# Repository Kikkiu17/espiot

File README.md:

# espiot
A small board built to measure current and voltage of an appliance.<br />
This board was used as a testbed for STM32 ADC oversampler, UART and DMA.<br />
To measure current and voltage values, a 12-bit ADC was used, with an oversampling ratio of 256x and an 8-bit shift to obtain efficient data averaging - this provides stable readings, along with a sampling time of 3.5 cycles for current and 79.5 cycles for voltage. DMA was also used to transfer all the ADC readings into memory without performance losses.

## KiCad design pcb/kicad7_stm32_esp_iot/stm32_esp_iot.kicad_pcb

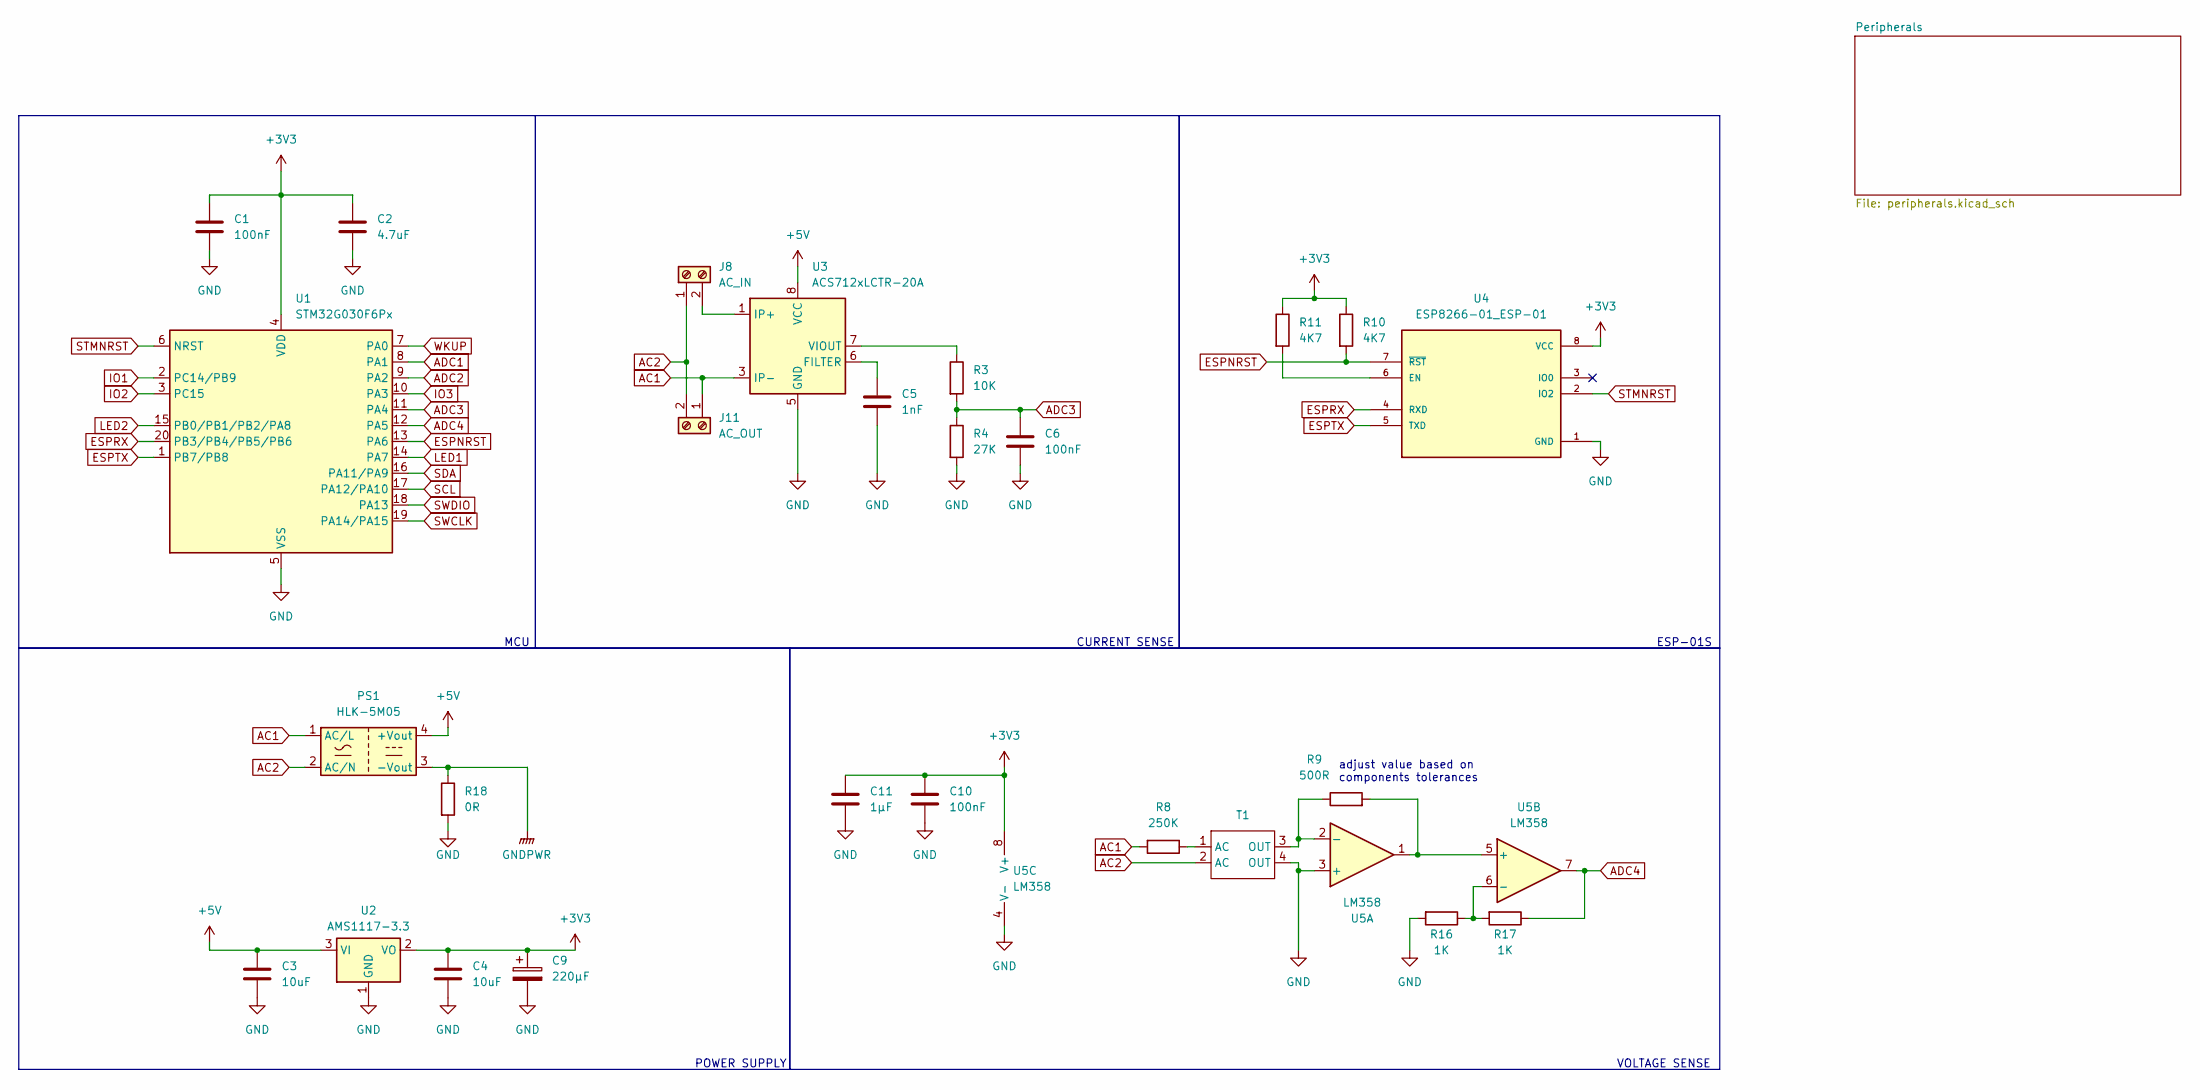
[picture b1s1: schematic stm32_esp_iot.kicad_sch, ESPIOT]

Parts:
C1, C6, C10: 100nF; C_0603_1608Metric
C2: 4.7uF; C_0603_1608Metric
C3, C4: 10uF; C_0603_1608Metric
C5: 1nF; C_0603_1608Metric
C9: 220µF; CP_Radial_D6.3mm_P2.50mm
C11: 1µF; C_0603_1608Metric
J8: AC_IN; mors_2p
J11: AC_OUT; mors_2p
PS1: HLK-5M05; Converter_ACDC_HiLink_HLK-5Mxx
R3: 10K; R_0603_1608Metric
R4: 27K; R_0603_1608Metric
R8: 250K; R_1206_3216Metric
R9: 500R; R_0603_1608Metric
R10, R11: 4K7; R_0603_1608Metric
R16, R17: 1K; R_0603_1608Metric
R18: 0R; R_1206_3216Metric
T1: ZMPT107
U1: STM32G030F6Px; TSSOP-20_4.4x6.5mm_P0.65mm
U2: AMS1117-3.3; SOT-223-3_TabPin2
U3: ACS712xLCTR-20A; SOIC-8_3.9x4.9mm_P1.27mm
U4: ESP8266-01_ESP-01; esp-01s; PARTREV V1.2
U5: LM358; DIP-8_W7.62mm

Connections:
+3V3: C1.1, C2.1, C4.1, C9.1, C10.1, C11.1, R10.1, R11.1, U1.4 (VDD), U2.2 (VO), U4.8 (VCC), U5.8 (V+); also elsewhere on the board
+5V: C3.1, PS1.4 (+Vout), U2.3 (VI), U3.8 (VCC); also elsewhere on the board
AC1: J11.1, PS1.1 (AC/L), R8.2, U3.3 (IP-), U3.4 (IP-)
AC2: J8.1, J11.2, PS1.2 (AC/N), T1.2 (AC)
ADC1: U1.8 (PA1); also elsewhere on the board
ADC2: U1.9 (PA2); also elsewhere on the board
ADC3: C6.1, R3.2, R4.1, U1.11 (PA4)
ADC4: R17.1, U1.12 (PA5), U5.7
ESPNRST: R10.2, U1.13 (PA6), U4.7 (~RST)
ESPRX: U1.20 (PB3/PB4/PB5/PB6), U4.4 (RXD)
ESPTX: U1.1 (PB7/PB8), U4.5 (TXD)
GND: C1.2, C2.2, C3.2, C4.2, C5.2, C6.2, C9.2, C10.2, C11.2, R4.2, R16.2, R18.2, T1.4 (OUT), U1.5 (VSS), U2.1 (GND), U3.5 (GND), U4.1 (GND), U5.3 (+), U5.4 (V-); also elsewhere on the board
GNDPWR: PS1.3 (-Vout), R18.1; also elsewhere on the board
IO1: U1.2 (PC14/PB9); also elsewhere on the board
IO2: U1.3 (PC15); also elsewhere on the board
IO3: U1.10 (PA3); also elsewhere on the board
LED1: U1.14 (PA7); also elsewhere on the board
LED2: U1.15 (PB0/PB1/PB2/PA8); also elsewhere on the board
unnamed: J8.2, U3.1 (IP+), U3.2 (IP+)
unnamed: R8.1, T1.1 (AC)
unnamed: C5.1, U3.6 (FILTER)
unnamed: R3.1, U3.7 (VIOUT)
unnamed: R11.2, U4.6 (EN)
unnamed: R9.1, T1.3 (OUT), U5.2 (-)
unnamed: R9.2, U5.1, U5.5 (+)
unnamed: R16.1, R17.2, U5.6 (-)
SCL: U1.17 (PA12/PA10); also elsewhere on the board
SDA: U1.16 (PA11/PA9); also elsewhere on the board
STMNRST: U1.6 (NRST), U4.2 (IO2)
SWCLK: U1.19 (PA14/PA15); also elsewhere on the board
SWDIO: U1.18 (PA13); also elsewhere on the board
WKUP: U1.7 (PA0); also elsewhere on the board

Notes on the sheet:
adjust value based on components tolerances
MCU
VOLTAGE SENSE
CURRENT SENSE
ESP-01S
POWER SUPPLY

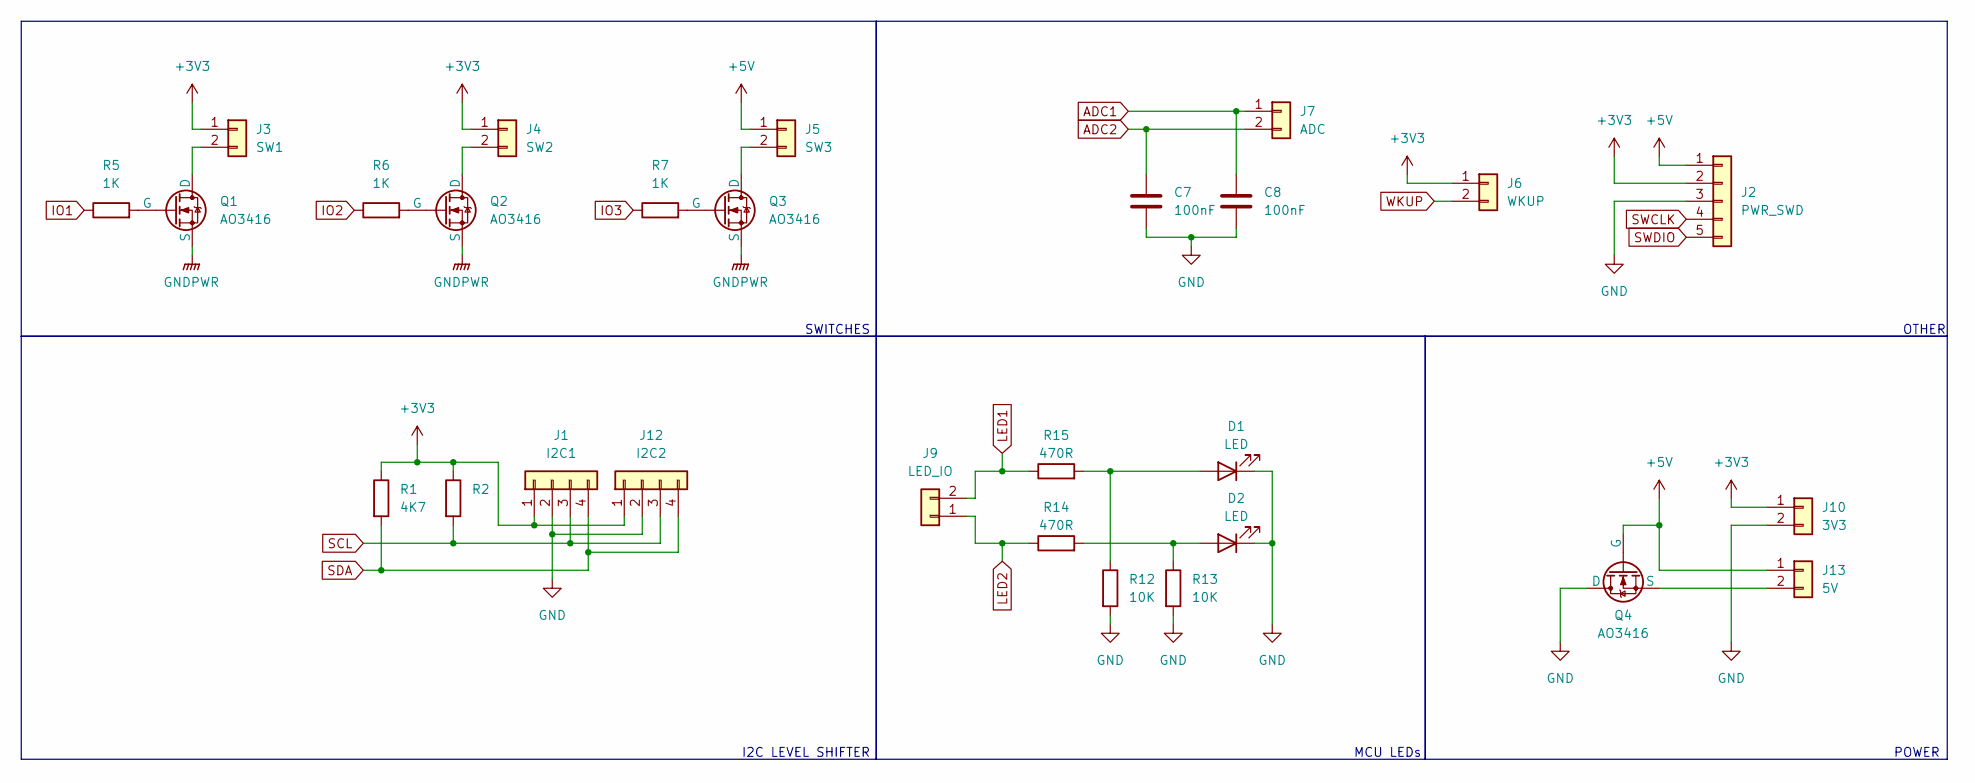
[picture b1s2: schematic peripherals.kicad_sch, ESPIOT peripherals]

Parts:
C7, C8: 100nF; C_0603_1608Metric
D1: LED; LED_0805_2012Metric
D2: LED; LED_0603_1608Metric
J1: I2C1; JST_EH_B4B-EH-A_1x04_P2.50mm_Vertical
J2: PWR_SWD; JST_EH_B5B-EH-A_1x05_P2.50mm_Vertical
J3: SW1; JST_EH_B2B-EH-A_1x02_P2.50mm_Vertical
J4: SW2; JST_EH_B2B-EH-A_1x02_P2.50mm_Vertical
J5: SW3; JST_EH_B2B-EH-A_1x02_P2.50mm_Vertical
J6: WKUP; JST_EH_B2B-EH-A_1x02_P2.50mm_Vertical
J7: ADC; JST_EH_B2B-EH-A_1x02_P2.50mm_Vertical
J9: LED_IO; JST_EH_B2B-EH-A_1x02_P2.50mm_Vertical
J10: 3V3; JST_EH_B2B-EH-A_1x02_P2.50mm_Vertical
J12: I2C2; JST_EH_B4B-EH-A_1x04_P2.50mm_Vertical
J13: 5V; JST_EH_B2B-EH-A_1x02_P2.50mm_Vertical
Q1, Q2, Q3, Q4: AO3416; SOT-23
R1, R2: 4K7; R_0603_1608Metric
R5, R6, R7: 1K; R_0603_1608Metric
R12, R13: 10K; R_0603_1608Metric
R14, R15: 470R; R_0603_1608Metric

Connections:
+3V3: J1.1, J2.2, J3.1, J4.1, J6.1, J10.1, J12.1, R1.1, R2.1; also elsewhere on the board
+5V: J2.1, J5.1, J13.1, Q4.2 (G); also elsewhere on the board
ADC1: C8.1, J7.1; also elsewhere on the board
ADC2: C7.1, J7.2; also elsewhere on the board
GND: C7.2, C8.2, D1.1 (K), D2.1 (K), J1.2, J2.3, J10.2, J12.2, Q4.1 (D), R12.2, R13.2; also elsewhere on the board
GNDPWR: Q1.3 (S), Q2.3 (S), Q3.3 (S); also elsewhere on the board
IO1: R5.1; also elsewhere on the board
IO2: R6.1; also elsewhere on the board
IO3: R7.1; also elsewhere on the board
LED1: J9.2, R15.1; also elsewhere on the board
LED2: J9.1, R14.1; also elsewhere on the board
unnamed: D1.2 (A), R12.1, R15.2
unnamed: D2.2 (A), R13.1, R14.2
unnamed: J3.2, Q1.1 (D)
unnamed: J4.2, Q2.1 (D)
unnamed: J5.2, Q3.1 (D)
unnamed: J13.2, Q4.3 (S)
unnamed: Q1.2 (G), R5.2
unnamed: Q2.2 (G), R6.2
unnamed: Q3.2 (G), R7.2
SCL: J1.3, J12.3, R2.2; also elsewhere on the board
SDA: J1.4, J12.4, R1.2; also elsewhere on the board
SWCLK: J2.4; also elsewhere on the board
SWDIO: J2.5; also elsewhere on the board
WKUP: J6.2; also elsewhere on the board

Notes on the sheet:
POWER
SWITCHES
MCU LEDs
I2C LEVEL SHIFTER
OTHER

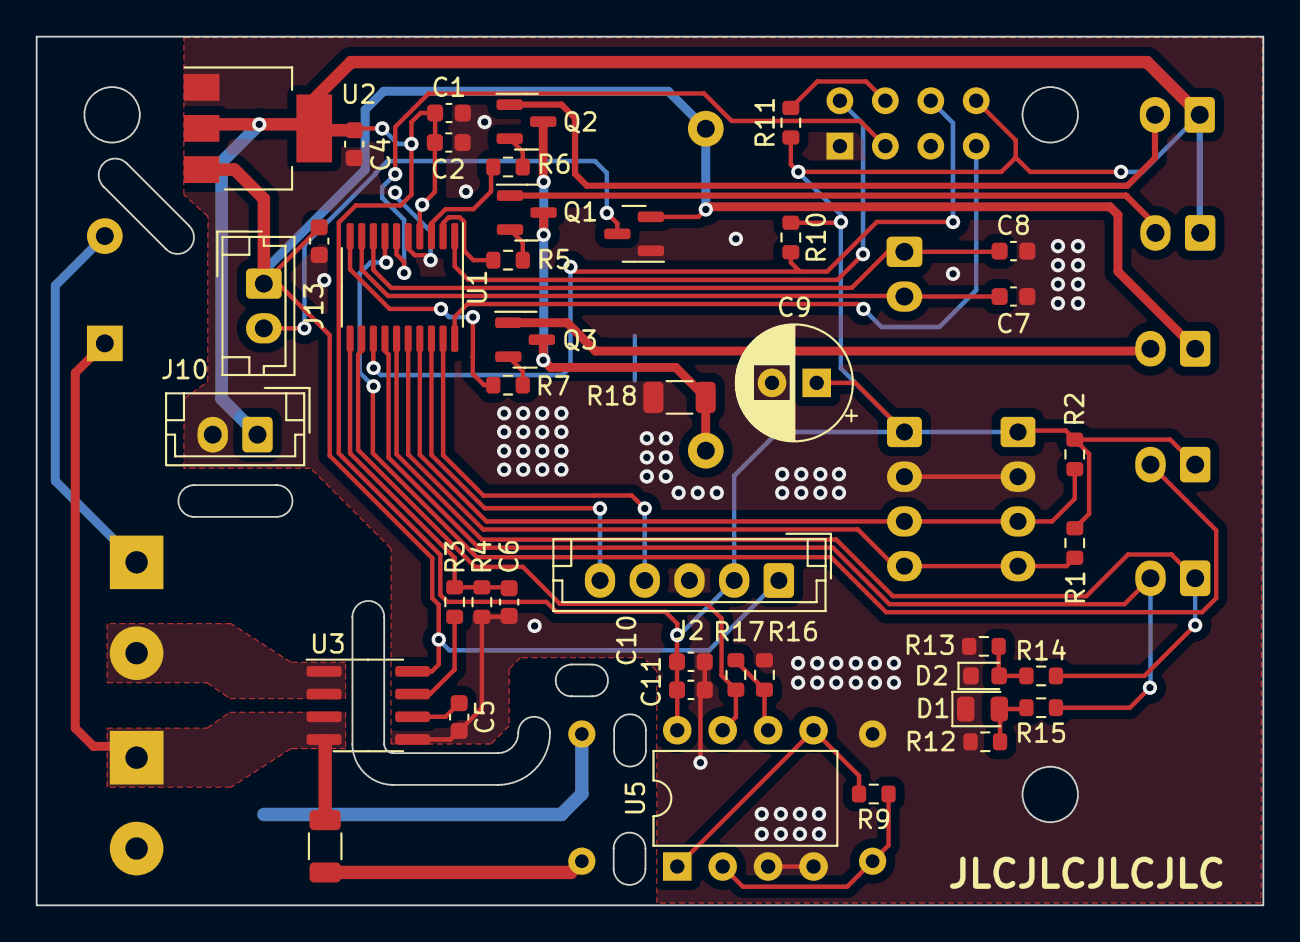
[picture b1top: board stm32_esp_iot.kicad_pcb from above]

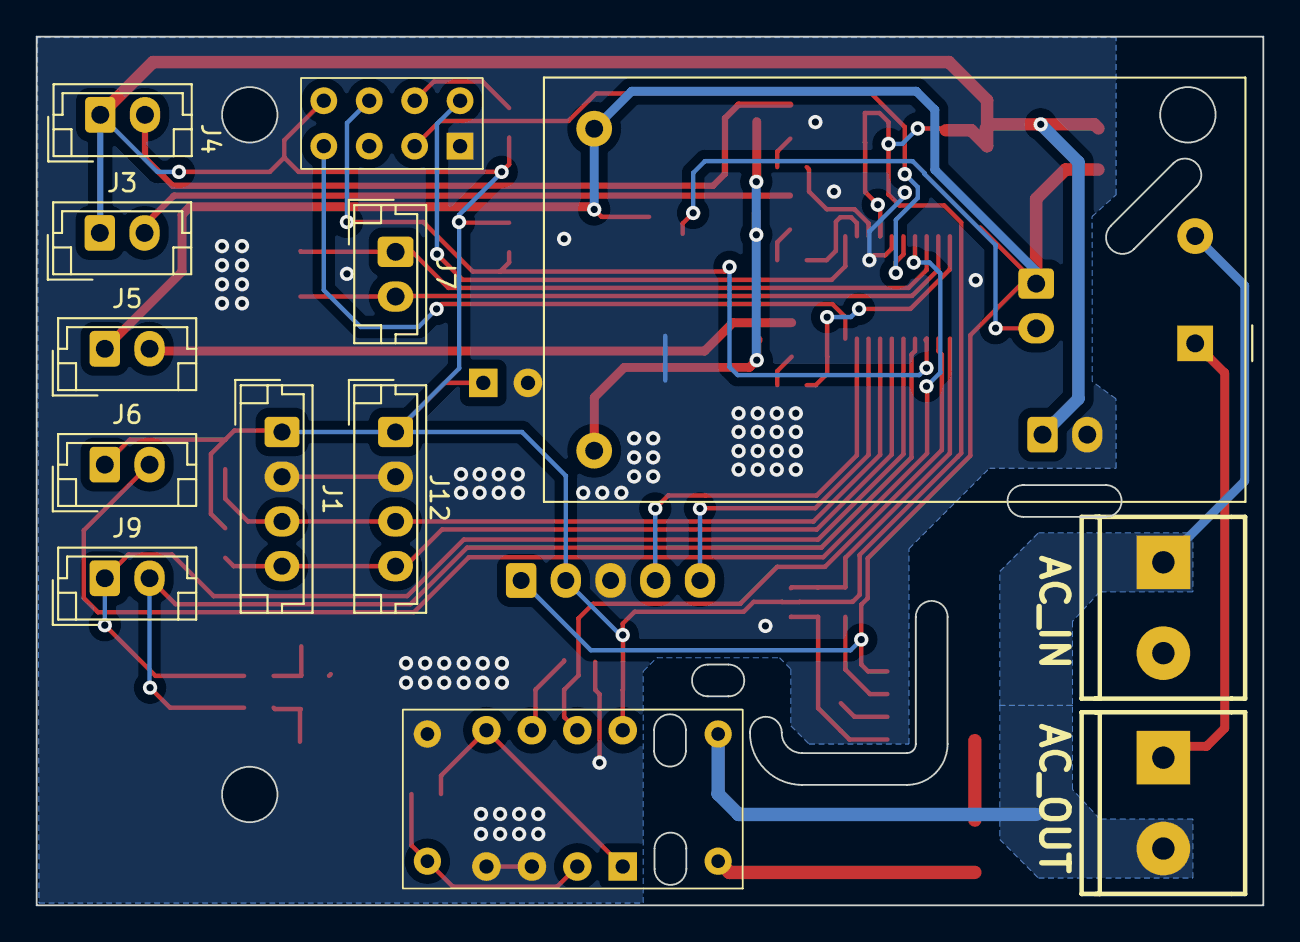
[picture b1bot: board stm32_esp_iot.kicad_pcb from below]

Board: 2 copper layers, 68.6 x 48.6 mm, 55 parts (13 on the bottom side), 41 nets.

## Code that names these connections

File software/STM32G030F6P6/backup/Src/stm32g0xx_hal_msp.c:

/* USER CODE BEGIN Header */
/**
  ******************************************************************************
  * @file         stm32g0xx_hal_msp.c
  * @brief        This file provides code for the MSP Initialization
  *               and de-Initialization codes.
  ******************************************************************************
  * @attention
  *
  * Copyright (c) 2024 STMicroelectronics.
  * All rights reserved.
  *
  * This software is licensed under terms that can be found in the LICENSE file
  * in the root directory of this software component.
  * If no LICENSE file comes with this software, it is provided AS-IS.
  *
  ******************************************************************************
  */
/* USER CODE END Header */

/* Includes ------------------------------------------------------------------*/
#include "main.h"

/* USER CODE BEGIN Includes */

/* USER CODE END Includes */
extern DMA_HandleTypeDef hdma_adc1;

extern DMA_HandleTypeDef hdma_usart1_rx;

/* Private typedef -----------------------------------------------------------*/
/* USER CODE BEGIN TD */

/* USER CODE END TD */

/* Private define ------------------------------------------------------------*/
/* USER CODE BEGIN Define */

/* USER CODE END Define */

/* Private macro -------------------------------------------------------------*/
/* USER CODE BEGIN Macro */

/* USER CODE END Macro */

/* Private variables ---------------------------------------------------------*/
/* USER CODE BEGIN PV */

/* USER CODE END PV */

/* Private function prototypes -----------------------------------------------*/
/* USER CODE BEGIN PFP */

/* USER CODE END PFP */

/* External functions --------------------------------------------------------*/
/* USER CODE BEGIN ExternalFunctions */

/* USER CODE END ExternalFunctions */

/* USER CODE BEGIN 0 */

/* USER CODE END 0 */
/**
  * Initializes the Global MSP.
  */
void HAL_MspInit(void)
{
  /* USER CODE BEGIN MspInit 0 */

  /* USER CODE END MspInit 0 */

  __HAL_RCC_SYSCFG_CLK_ENABLE();
  __HAL_RCC_PWR_CLK_ENABLE();

  /* System interrupt init*/

  /* USER CODE BEGIN MspInit 1 */

  /* USER CODE END MspInit 1 */
}

/**
* @brief ADC MSP Initialization
* This function configures the hardware resources used in this example
* @param hadc: ADC handle pointer
* @retval None
*/
void HAL_ADC_MspInit(ADC_HandleTypeDef* hadc)
{
  GPIO_InitTypeDef GPIO_InitStruct = {0};
  if(hadc->Instance==ADC1)
  {
  /* USER CODE BEGIN ADC1_MspInit 0 */

  /* USER CODE END ADC1_MspInit 0 */
    /* Peripheral clock enable */
    __HAL_RCC_ADC_CLK_ENABLE();

    __HAL_RCC_GPIOA_CLK_ENABLE();
    /**ADC1 GPIO Configuration
    PA4     ------> ADC1_IN4
    PA5     ------> ADC1_IN5
    */
    GPIO_InitStruct.Pin = GPIO_PIN_4|GPIO_PIN_5;
    GPIO_InitStruct.Mode = GPIO_MODE_ANALOG;
    GPIO_InitStruct.Pull = GPIO_NOPULL;
    HAL_GPIO_Init(GPIOA, &GPIO_InitStruct);

    /* ADC1 DMA Init */
    /* ADC1 Init */
    hdma_adc1.Instance = DMA1_Channel1;
    hdma_adc1.Init.Request = DMA_REQUEST_ADC1;
    hdma_adc1.Init.Direction = DMA_PERIPH_TO_MEMORY;
    hdma_adc1.Init.PeriphInc = DMA_PINC_DISABLE;
    hdma_adc1.Init.MemInc = DMA_MINC_ENABLE;
    hdma_adc1.Init.PeriphDataAlignment = DMA_PDATAALIGN_HALFWORD;
    hdma_adc1.Init.MemDataAlignment = DMA_MDATAALIGN_HALFWORD;
    hdma_adc1.Init.Mode = DMA_CIRCULAR;
    hdma_adc1.Init.Priority = DMA_PRIORITY_LOW;
    if (HAL_DMA_Init(&hdma_adc1) != HAL_OK)
    {
      Error_Handler();
    }

    __HAL_LINKDMA(hadc,DMA_Handle,hdma_adc1);

  /* USER CODE BEGIN ADC1_MspInit 1 */

  /* USER CODE END ADC1_MspInit 1 */
  }

}

/**
* @brief ADC MSP De-Initialization
* This function freeze the hardware resources used in this example
* @param hadc: ADC handle pointer
* @retval None
*/
void HAL_ADC_MspDeInit(ADC_HandleTypeDef* hadc)
{
  if(hadc->Instance==ADC1)
  {
  /* USER CODE BEGIN ADC1_MspDeInit 0 */

  /* USER CODE END ADC1_MspDeInit 0 */
    /* Peripheral clock disable */
    __HAL_RCC_ADC_CLK_DISABLE();

    /**ADC1 GPIO Configuration
    PA4     ------> ADC1_IN4
    PA5     ------> ADC1_IN5
    */
    HAL_GPIO_DeInit(GPIOA, GPIO_PIN_4|GPIO_PIN_5);

    /* ADC1 DMA DeInit */
    HAL_DMA_DeInit(hadc->DMA_Handle);
  /* USER CODE BEGIN ADC1_MspDeInit 1 */

  /* USER CODE END ADC1_MspDeInit 1 */
  }

}

/**
* @brief TIM_Base MSP Initialization
* This function configures the hardware resources used in this example
* @param htim_base: TIM_Base handle pointer
* @retval None
*/
void HAL_TIM_Base_MspInit(TIM_HandleTypeDef* htim_base)
{
  if(htim_base->Instance==TIM3)
  {
  /* USER CODE BEGIN TIM3_MspInit 0 */

  /* USER CODE END TIM3_MspInit 0 */
    /* Peripheral clock enable */
    __HAL_RCC_TIM3_CLK_ENABLE();
  /* USER CODE BEGIN TIM3_MspInit 1 */

  /* USER CODE END TIM3_MspInit 1 */
  }

}

/**
* @brief TIM_Base MSP De-Initialization
* This function freeze the hardware resources used in this example
* @param htim_base: TIM_Base handle pointer
* @retval None
*/
void HAL_TIM_Base_MspDeInit(TIM_HandleTypeDef* htim_base)
{
  if(htim_base->Instance==TIM3)
  {
  /* USER CODE BEGIN TIM3_MspDeInit 0 */

  /* USER CODE END TIM3_MspDeInit 0 */
    /* Peripheral clock disable */
    __HAL_RCC_TIM3_CLK_DISABLE();
  /* USER CODE BEGIN TIM3_MspDeInit 1 */

  /* USER CODE END TIM3_MspDeInit 1 */
  }

}

/**
* @brief UART MSP Initialization
* This function configures the hardware resources used in this example
* @param huart: UART handle pointer
* @retval None
*/
void HAL_UART_MspInit(UART_HandleTypeDef* huart)
{
  GPIO_InitTypeDef GPIO_InitStruct = {0};
  RCC_PeriphCLKInitTypeDef PeriphClkInit = {0};
  if(huart->Instance==USART1)
  {
  /* USER CODE BEGIN USART1_MspInit 0 */

  /* USER CODE END USART1_MspInit 0 */

  /** Initializes the peripherals clocks
  */
    PeriphClkInit.PeriphClockSelection = RCC_PERIPHCLK_USART1;
    PeriphClkInit.Usart1ClockSelection = RCC_USART1CLKSOURCE_PCLK1;
    if (HAL_RCCEx_PeriphCLKConfig(&PeriphClkInit) != HAL_OK)
    {
      Error_Handler();
    }

    /* Peripheral clock enable */
    __HAL_RCC_USART1_CLK_ENABLE();

    __HAL_RCC_GPIOB_CLK_ENABLE();
    /**USART1 GPIO Configuration
    PB7     ------> USART1_RX
    PB6     ------> USART1_TX
    */
    GPIO_InitStruct.Pin = GPIO_PIN_7|GPIO_PIN_6;
    GPIO_InitStruct.Mode = GPIO_MODE_AF_PP;
    GPIO_InitStruct.Pull = GPIO_NOPULL;
    GPIO_InitStruct.Speed = GPIO_SPEED_FREQ_LOW;
    GPIO_InitStruct.Alternate = GPIO_AF0_USART1;
    HAL_GPIO_Init(GPIOB, &GPIO_InitStruct);

    /* USART1 DMA Init */
    /* USART1_RX Init */
    hdma_usart1_rx.Instance = DMA1_Channel2;
    hdma_usart1_rx.Init.Request = DMA_REQUEST_USART1_RX;
    hdma_usart1_rx.Init.Direction = DMA_PERIPH_TO_MEMORY;
    hdma_usart1_rx.Init.PeriphInc = DMA_PINC_DISABLE;
    hdma_usart1_rx.Init.MemInc = DMA_MINC_ENABLE;
    hdma_usart1_rx.Init.PeriphDataAlignment = DMA_PDATAALIGN_BYTE;
    hdma_usart1_rx.Init.MemDataAlignment = DMA_MDATAALIGN_BYTE;
    hdma_usart1_rx.Init.Mode = DMA_CIRCULAR;
    hdma_usart1_rx.Init.Priority = DMA_PRIORITY_LOW;
    if (HAL_DMA_Init(&hdma_usart1_rx) != HAL_OK)
    {
      Error_Handler();
    }

    __HAL_LINKDMA(huart,hdmarx,hdma_usart1_rx);

  /* USER CODE BEGIN USART1_MspInit 1 */

  /* USER CODE END USART1_MspInit 1 */
  }

}

/**
* @brief UART MSP De-Initialization
* This function freeze the hardware resources used in this example
* @param huart: UART handle pointer
* @retval None
*/
void HAL_UART_MspDeInit(UART_HandleTypeDef* huart)
{
  if(huart->Instance==USART1)
  {
  /* USER CODE BEGIN USART1_MspDeInit 0 */

  /* USER CODE END USART1_MspDeInit 0 */
    /* Peripheral clock disable */
    __HAL_RCC_USART1_CLK_DISABLE();

    /**USART1 GPIO Configuration
    PB7     ------> USART1_RX
    PB6     ------> USART1_TX
    */
    HAL_GPIO_DeInit(GPIOB, GPIO_PIN_7|GPIO_PIN_6);

    /* USART1 DMA DeInit */
    HAL_DMA_DeInit(huart->hdmarx);
  /* USER CODE BEGIN USART1_MspDeInit 1 */

  /* USER CODE END USART1_MspDeInit 1 */
  }

}

/* USER CODE BEGIN 1 */

/* USER CODE END 1 */

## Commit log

2024-04-23 Project upload
2025-09-16 Updated firmware to SNSE latest version
2025-09-16 Updated app screenshot
2025-09-16 Removed BOM
2025-09-28 Fixed critical bug
2025-10-03 Fixed write past array length
2025-10-03 Fixed name reading issue
2025-10-22 Improved safety
2025-11-08 Fixed comm bugs
2025-11-08 Fixed setName bug
2025-11-30 Added calibration values
2025-12-02 Added static IP (latest SNSE update)
2025-12-06 Fixed ESP start problem
2026-02-05 Updated ESP AT firmware
